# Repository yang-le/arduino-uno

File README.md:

# arduino-uno

## Front

### 3d

### 2d

### Cu

### Pad

### Silk

## Back

### 3d

### 2d

### Cu

### Pad

### Silk

## Misc

### Edge

### Drill

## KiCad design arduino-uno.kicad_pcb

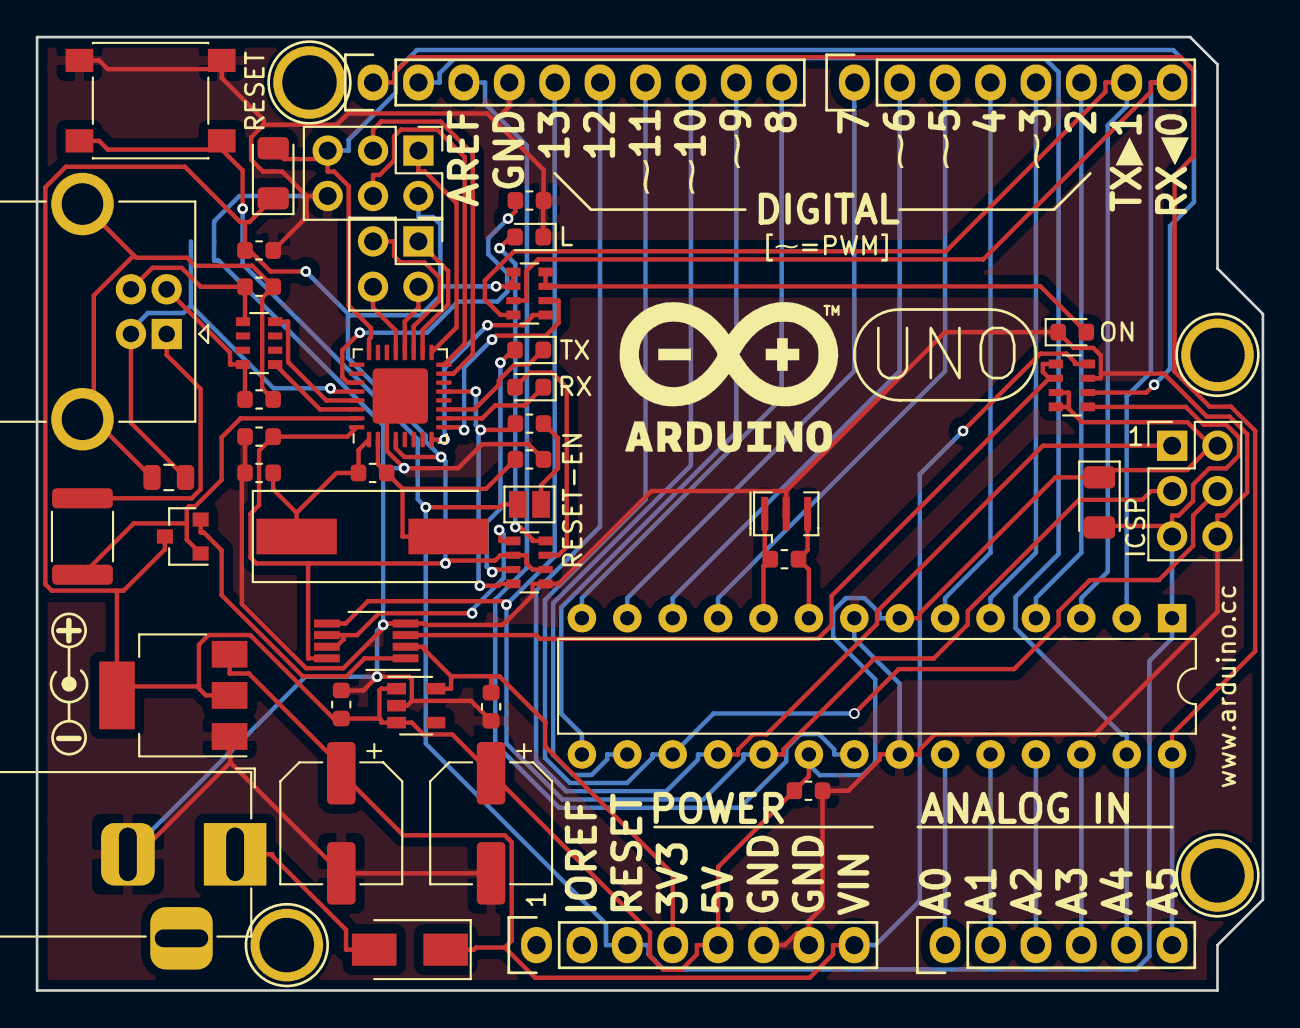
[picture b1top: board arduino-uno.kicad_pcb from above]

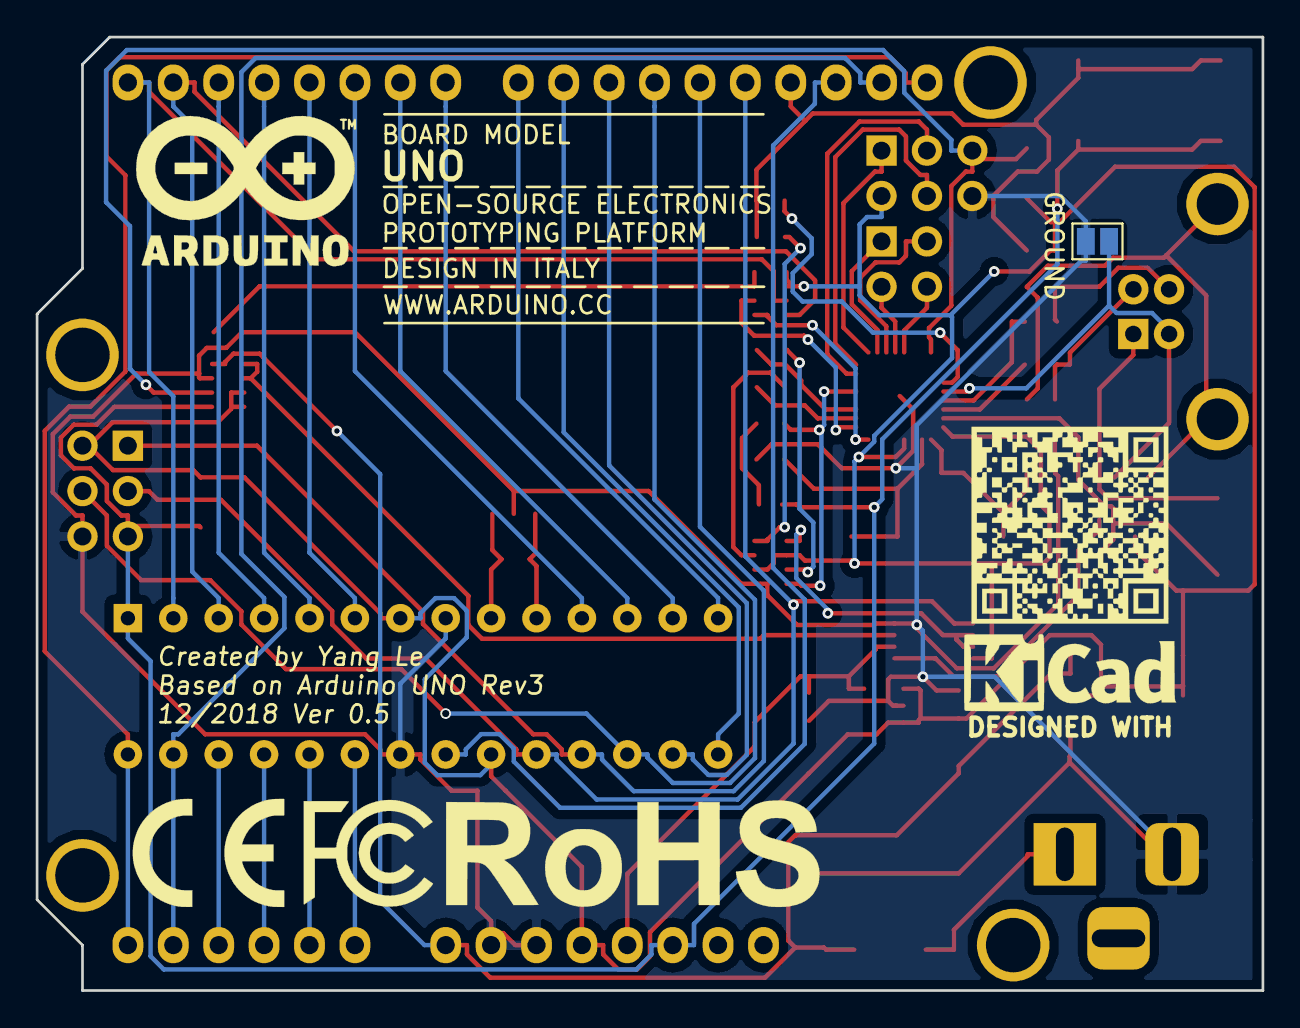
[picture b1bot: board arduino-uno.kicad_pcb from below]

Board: 2 copper layers, 68.6 x 53.3 mm, 60 parts (7 on the bottom side), 61 nets.

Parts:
C1, C2: 47u; CP_Elec_6.3x5.9
C3, C4, C8, C10, C11: 100n; C_0603_1608Metric
C5, C9: 1u; C_0603_1608Metric
C6, C7: 22p; C_0603_1608Metric
D1: M7; D_SMA
D3, D6: CD1206-S01575; D_1206_3216Metric
F1: MF-MSMF050-2; Fuse_1812_4532Metric
FB1: BLM21; L_0805_2012Metric
G1, G2, G3: LOGO
GROUND: GROUND; SolderJumper-2_P1.3mm_Open_Pad1.0x1.5mm
ICSP: Conn_02x03; PinHeader_2x03_P2.54mm_Vertical
J1: Jack-DC; BarrelJack_Horizontal
J2: USB_B; USB_B_OST_USB-B1HSxx_Horizontal
J3: Conn_02x03; PinHeader_2x03_P2.54mm_Vertical
J4: Conn_02x02; PinHeader_2x02_P2.54mm_Vertical
L: L; LED_0603_1608Metric
ON: ON; LED_0603_1608Metric
P1: Power; Socket_Strip_Arduino_1x08
P2: Analog; Socket_Strip_Arduino_1x06
P3: Digital; Socket_Strip_Arduino_1x10
P4: Digital; Socket_Strip_Arduino_1x08
P5, P6, P7, P8: CONN_01X01; Arduino_1pin
Q1: FDN340P; SOT-23
R1, R2: 1M; R_0603_1608Metric
REF1: Symbol_Barrel_Polarity
REF2: CE-Logo_8.5x6mm_SilkScreen
REF3: FCC-Logo_7.3x6mm_SilkScreen
REF4: RoHS-Logo_6mm_SilkScreen
REF5: KiCAD Logo; Symbol_KiCAD-Logo_CopperAndSilkScreenTop
RESET: RESET; SW_SPST_PTS645
RESET-EN: RESET-EN; SolderJumper-2_P1.3mm_Open_Pad1.0x1.5mm
RN1: 10K; R_Array_Convex_4x0603
RN2, RN4: 1K; R_Array_Convex_4x0603
RN3: 22; R_Array_Convex_4x0603
RV1, RV2: CG0603MLC-05E; R_0603_1608Metric
RX: RX; LED_0603_1608Metric
TX: TX; LED_0603_1608Metric
U1: NCP1117-5.0; SOT-223-3_TabPin2
U2: LMV358IDGKR; VSSOP-8_3.0x3.0mm_P0.65mm
U3: LP2985-3.3; SOT-23-5
U4: ATmega16U2-MU; QFN-32-1EP_5x5mm_P0.5mm_EP3.1x3.1mm
U5: ATmega328P-PU; DIP-28_W7.62mm
Y1: Crystal; Crystal_SMD_HC49-SD
Y2: CSTCE16M0V53-R0; Resonator_SMD_muRata_CSTxExxV-3Pin_3.0x1.1mm

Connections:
+3V3: C5.1, P1.4, U2.2, U3.5
+5V: C2.1, C3.1, C4.1, C8.1, C11.1, D3.1, D6.1, ICSP.2, J3.2, P1.5, Q1.3, RN1.3, RN1.4, RN2.2, RN2.6, RN4.5, RN4.6, U1.2, U2.8, U3.1, U3.3, U4.4, U4.32, U5.7, U5.20
/Main/0(Rx): P4.8, RN4.7, U5.2
/Main/1(Tx): P4.7, RN4.8, U5.3
/Main/2: P4.6, U5.4
/Main/3(**): P4.5, U5.5
/Main/4: P4.4, U5.6
/Main/5(**): P4.3, U5.11
/Main/6(**): P4.2, U5.12
/Main/7: P4.1, U5.13
/Main/8: P3.10, U5.14
/Main/9(**): P3.9, U5.15
/Main/10(**/SS): P3.8, U5.16
/Main/11(**/MOSI): ICSP.4, P3.7, U5.17
/Main/12(MISO): ICSP.1, P3.6, U5.18
/Main/13(SCK): ICSP.3, P3.5, U2.5, U5.19
/Main/A0: P2.1, U5.23
/Main/A1: P2.2, U5.24
/Main/A2: P2.3, U5.25
/Main/A3: P2.4, U5.26
/Main/A4(SDA): P2.5, P3.2, U5.27
/Main/A5(SCL): P2.6, P3.1, U5.28
/Main/AREF: P3.3, U5.21
/Main/DTR: C10.2, RN2.4, U4.13
/Main/M8RXD: RN4.2, U4.9
/Main/M8TXD: RN4.1, U4.8
/Main/Reset: D6.2, ICSP.5, P1.3, RESET.1, RESET-EN.1, RN1.5, U5.1
/Main/VIN: C1.1, D1.1, P1.8, RN1.8, U1.3
/Power/USBVCC: F1.1, Q1.1, U4.31
/USB/MISO2: J3.1, U4.17
/USB/MOSI2: J3.4, U4.16
/USB/SCK2: J3.3, U4.15
GND: C1.2, C2.2, C3.2, C4.2, C5.2, C6.2, C7.2, C8.2, C9.2, C11.2, GROUND.2, ICSP.6, J1.2, J3.6, L.1, ON.1, P1.6, P1.7, P3.4, RESET.2, RN1.7, RN2.5, U1.1, U2.4, U3.2, U4.3, U4.33, U5.8, U5.22, Y2.2
unnamed: C6.1, R1.1, U4.1, Y1.1
unnamed: C7.1, R1.2, U4.2, Y1.2
unnamed: C9.1, U4.27
unnamed: C10.1, RESET-EN.2
unnamed: D1.2, J1.1
unnamed: ON.2, RN4.3, RN4.4
unnamed: D3.2, J3.5, RN1.6, U4.24
unnamed: TX.1, U4.11
unnamed: RN2.3, TX.2
unnamed: RX.1, U4.10
unnamed: RN2.7, RX.2
unnamed: L.2, RN2.8
unnamed: F1.2, J2.1
unnamed: FB1.1, J2.5, RV1.2, RV2.2
unnamed: FB1.2, GROUND.1, J2.4, U4.28
unnamed: J2.2, RN3.8, RV2.1
unnamed: J2.3, RN3.5, RV1.1
unnamed: J4.1, U4.18
unnamed: J4.2, U4.20
unnamed: J4.3, U4.19
unnamed: J4.4, U4.21
unnamed: Q1.2, U2.1
unnamed: R2.1, U5.9, Y2.3
unnamed: R2.2, U5.10, Y2.1
unnamed: RN1.1, RN1.2, U2.3
unnamed: RN2.1, U2.6, U2.7
unnamed: RN3.1, U4.30
unnamed: RN3.4, U4.29

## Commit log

2018-12-16 add .gitignore
2018-12-16 place finish
2018-12-16 route finish
2018-12-18 add logos
2018-12-19 more pics
2018-12-19 replace two Caps
2018-12-20 ready to fab
2018-12-20 add 3d shapes for usb & crystal
